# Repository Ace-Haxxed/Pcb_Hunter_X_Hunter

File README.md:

# Pcb_Hunter_X_Hunter

Yo Zohair Shaik here and this is my first PCB this pcb is something special to me since it has 2 of my fav characters from my fav anime.. Hunter X Hunter (I recommend you watch it it is peak fiction)

**Slack Username: @Ace Gmail: zohairshaik7@gmail.com Discord: autohackingcodes2097**

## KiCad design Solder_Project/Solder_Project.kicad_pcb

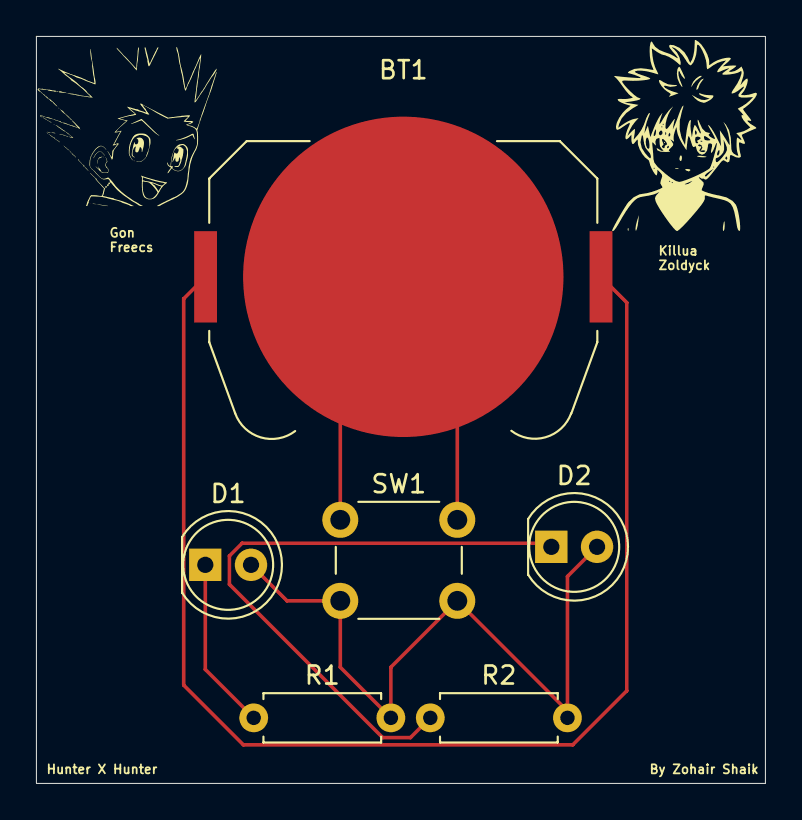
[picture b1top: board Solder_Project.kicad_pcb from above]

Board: 2 copper layers, 40.5 x 41.5 mm, 6 parts (0 on the bottom side), 4 nets.

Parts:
BT1: Battery_Cell; BatteryHolder_Keystone_3034_1x20mm
D1, D2: LED; LED_D5.0mm
R1, R2: R; R_Axial_DIN0207_L6.3mm_D2.5mm_P7.62mm_Horizontal
SW1: SW_Push; SW_PUSH_6mm

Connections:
GND: D1.2 (A), D2.2 (A), R1.2, R2.2, SW1.2
unnamed: BT1.2 (-), SW1.1
unnamed: D1.1 (K), R1.1
unnamed: D2.1 (K), R2.1
